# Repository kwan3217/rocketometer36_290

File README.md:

Moved to [GitHub](https://gitlab.com/kwan32171/rocketometer36_290)

This documents the data produced by the Rocketometer during NASA Sounding Rocket Flight 36.290, 2013 Oct 21.

# Encoding format
The data was captured and encoded in the form of CCSDS packets. The exact structure of each packet is most completely documented in the source code.

# Source code
The Rocketometer contains an LPC2148 ARM-based MCU with 512kiB flash memory. As this was far more memory than I needed for the firmware, I worked out a way to attach the source code of the firmware as well as the hardware design to the firmware itself. The Rocketometer spits this out into the packet stream as one of the first things it does at startup. How's that for configuration control?

The source code package is in the form of a ZPAQ TAR archive. The folder includes all the C++ source code, Makefiles, and such for rebuilding the firmware, which will be identical to the firmware carried on the flight with the exception of the date stamp on the firmware.

The hardware design is in the form of an Eagle CAD board and schematic, editable with the Eagle freeware version (as that is what it was designed with). It also includes a bill of materials in the form of Digikey catalog numbers for all parts used on the board.

The source code package is attached to the firmware, along with pointers to exactly where in the firmware the package begins and ends. This enables the firmware to copy a piece of itself into the packet stream as multiple CCSDS packets.

# Time Stamp
The firmware uses one of the MCU counter/timers for timing. This counter is a 32-bit unsigned number which starts at zero during firmware bootup, and counts up to one less than 3.6 billion counts exactly, at which point it resets to zero. The counter nominally runs at 60MHz, so this counter resets once every 60 seconds. Each time-sensitive packet (almost all of them except for some startup packets) have this count in it, and the packets are generated at such a rate that it is possible to unambiguously unwind the counter and get an exact number of counts since startup. Unfortunately the time of startup was not marked in any absolute time scale such as UTC, so absolute timing has to be inferred from timestamped events in the data.

# Sensor data
The sensor data stream consists of three separate streams of packets:
1. The Fast packet includes the MPU6050 3-axis acceleration, 3-axis rotation, and temperature readings, along with the ADXL377 3-axis high-acceleration readings. These were read once every 3 milliseconds and timestamped as indicated above.
2. The Compass packet includes the HMC5883 3-axis magnetic readouts. These were measured at a multiple of the Fast packet period (see the source code for details)
3. The BMP packet includes the BMP180 pressure and temperature readouts, both raw and calibrated into physical units.
4. The Power packet stream includes one packet each time the external power state changed (including one at startup).
5. The Vertical packet stream includes data on the vertical sensing fast/slow packet rate (see the source code for details). I have verified that this worked as intended, and that the entire flight was recorded at the fast rate.

# Packet storage
Packet storage was on a 16GB microSD card. Less than 1GB was used between the time I delivered the Rocketometer and the time it was returned to me.

# Power
The board consumes something around 100mA, not counting charging. The charger can use and additional 100mA. The system has an internal battery in the form of a 100mAh LiPo cell. The Rocketometer is powered externally by a 5V line from the rocket payload. It charges the battery with its on-board LiPo charging circuit as necessary when external power is available, and runs off the battery when external power is off. The on-board switch is not accessible, so the board is on whenever the rest of the rocket payload is on, and only turns off once its battery discharges. The battery is made safe by its standard integrated safety circuit and the dedicated LiPo charging circuit.

# The Flight
The Rocketometer was integrated with the rest of the rocket payload months before the flight. After that time, no human interaction whatsoever took place. It was returned to me for readout a couple of hours after the flight was completed. In that time, it recorded 65 files, one for each time it was power-cycled. The one containing the flight was file RKTO0620.SDS . This file contains 54.4 MB of data covering well over an hour, from about 35 minutes before the flight until well after impact. External power was cut 585 seconds after launch, and the on-board battery sustained it for the rest of the flight.

# Rail data
The file RKTO0620.SDS starts after the rail was raised to almost vertical. Other records were taken when the rail was horizontal, in particular RKTO0600.SDS. This data has been processed into the same tables and published. Interesting things such as orientation of the Rocketometer relative to the rail can be determined from that.

It would have been nice for the Rocketometer to have been recording while the rail was raised from horizontal to vertical. Unfortunately this did not happen. Maybe next time...

For whatever reason, it seems that no magnetic data was recorded while the rail was horizontal. Apparently magnetic data is not recorded when the board is recording at low rate.

# Rocketometer coordinate system
All sensors were co-aligned, so each individual sensor matches the whole Rocketometer frame. The Rocketometer was mounted close to the spin axis of the rocket, with the +Z axis pointed towards the tail. Consequently the thrust acceleration was primarily read out as a -Z acceleration. It should be parallel to that axis to within normal mechanical tolerances, almost certainly quite a bit better than 1°.

Based on the rail data, the +X axis of the Rocketometer was pointed almost straight down when the rocket was hanging horizontally from the rail.

In the flight after burnout but before spindown, the rocket was coasting well above the atmosphere and spinning with constant angular momentum, nearly around its long axis. Therefore the entire sensed acceleration is pure centripetal. Therefore, the distance and direction from the accelerometer to the spin axis can be measured. I did this once, but I wasn't sure about the signs and therefore didn't record it.

# Processing into tables
The packet stream format is not convenient or quick for import into IDL. For this purpose, a packet dumper, extractFast, was written in pure C which reads a Rocketometer data file, parses out each kind of packet, and writes each different apid into a different file. All the fast packets are together, all the slow packets, all the compass, all the source code, etc are each in their own file. Since the most common case is that each apid has a consistent length, this apid file can be read quickly into IDL by a read_binary, treating it as a 2D array of 16-bit integers, where rows are individual packets, and columns are fields in the packet.

Each packet is assigned a global sequence number, and this number is one of the things written to the APID file. With this sequence number, the order of different packets in different files can be determined.

These APID files are then imported into IDL, where the timestamps are normalized, values are converted in endian-ness as needed, and in general the packets are parsed. As this is an array operation, it can be done several orders of magnitude faster than parsing each packet individually in IDL.

The published tables have the timestamp normalized (cycle ambiguity fixed, converted into seconds, offset from power-on to launch subtracted) but otherwise the data is as recorded by the Rocketometer in flight. In particular, no translation from raw DNs to physical units is performed.

# Included files
* `RKTO0620.SDS.zip` - raw flight data file, PKZIP compressed
* `RKTO0600.SDS.zip` - raw rail data file, PKZIP compressed
* `firmware.tar.gz` - Firmware package, as flown (from RKTO0620.SDS) but zpaq uncompressed and gzip recompressed
* `extractFast.c` - C program described above
* `apid list.ods` - Some documentation of the packet format, not know to be completely up-to-date. Use the source code as the final authority.
* `import_fast.pro` - IDL program which converts extractFast output to CSV tables, among other things.
* `RKTO0620_csv.zip` - Compressed archive containing the following files
   * `RKTO0620_fast.csv` - Comma separated values, fast packets as described above
   * `RKTO0620_bmp.csv` - Comma separated values, BMP180 temperature and pressure readings, raw and calibrated into physical units by the Rocketometer in-flight
   * `RKTO0620_hmc.csv` - Comma separated values, HMC5883 magnetic readings, as described above.
* `RKTO0600_csv.zip` - Compressed archive containing the following files
   * `RKTO0600_fast.csv` - Comma separated values, fast packets as described above
   * `RKTO0600_bmp.csv` - Comma separated values, BMP180 temperature and pressure readings, raw and calibrated into physical units by the Rocketometer on-board

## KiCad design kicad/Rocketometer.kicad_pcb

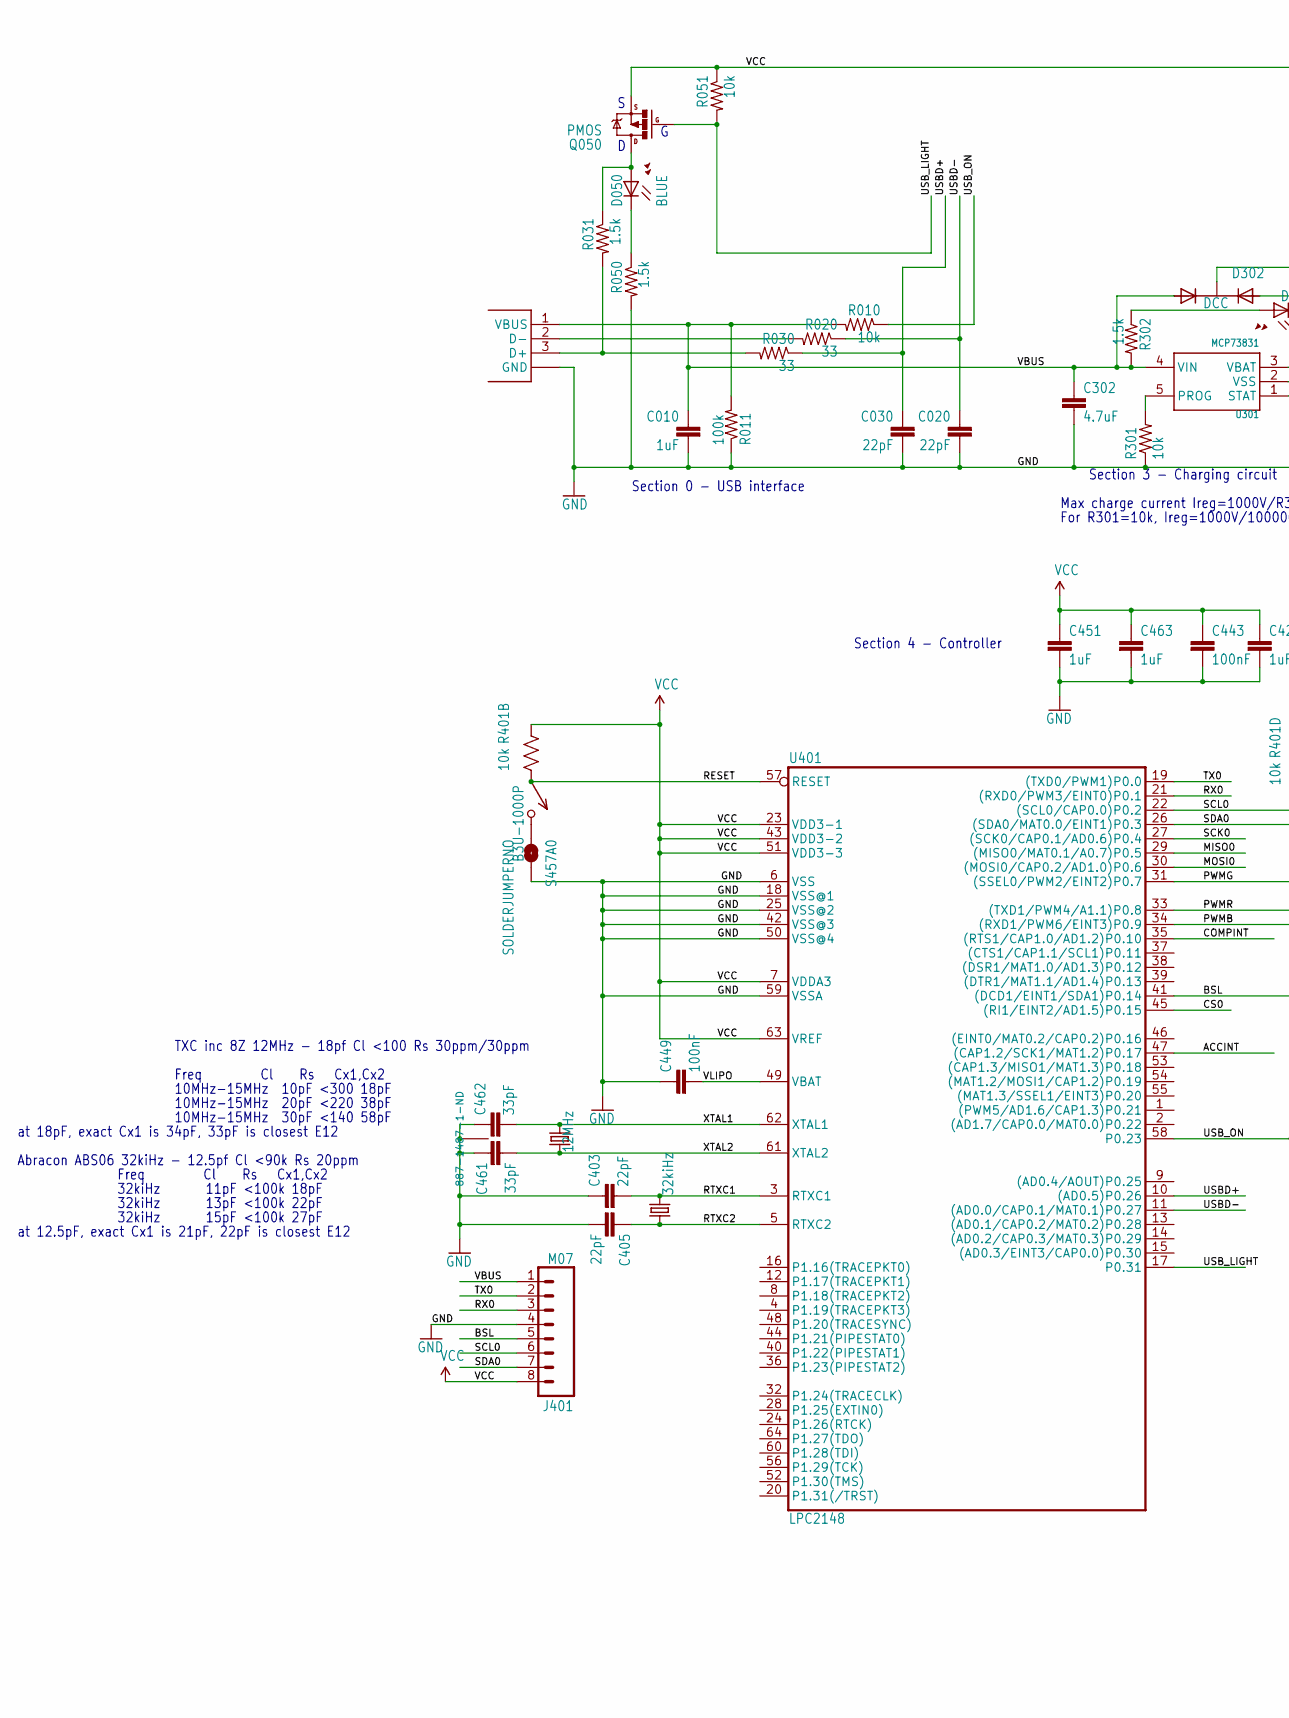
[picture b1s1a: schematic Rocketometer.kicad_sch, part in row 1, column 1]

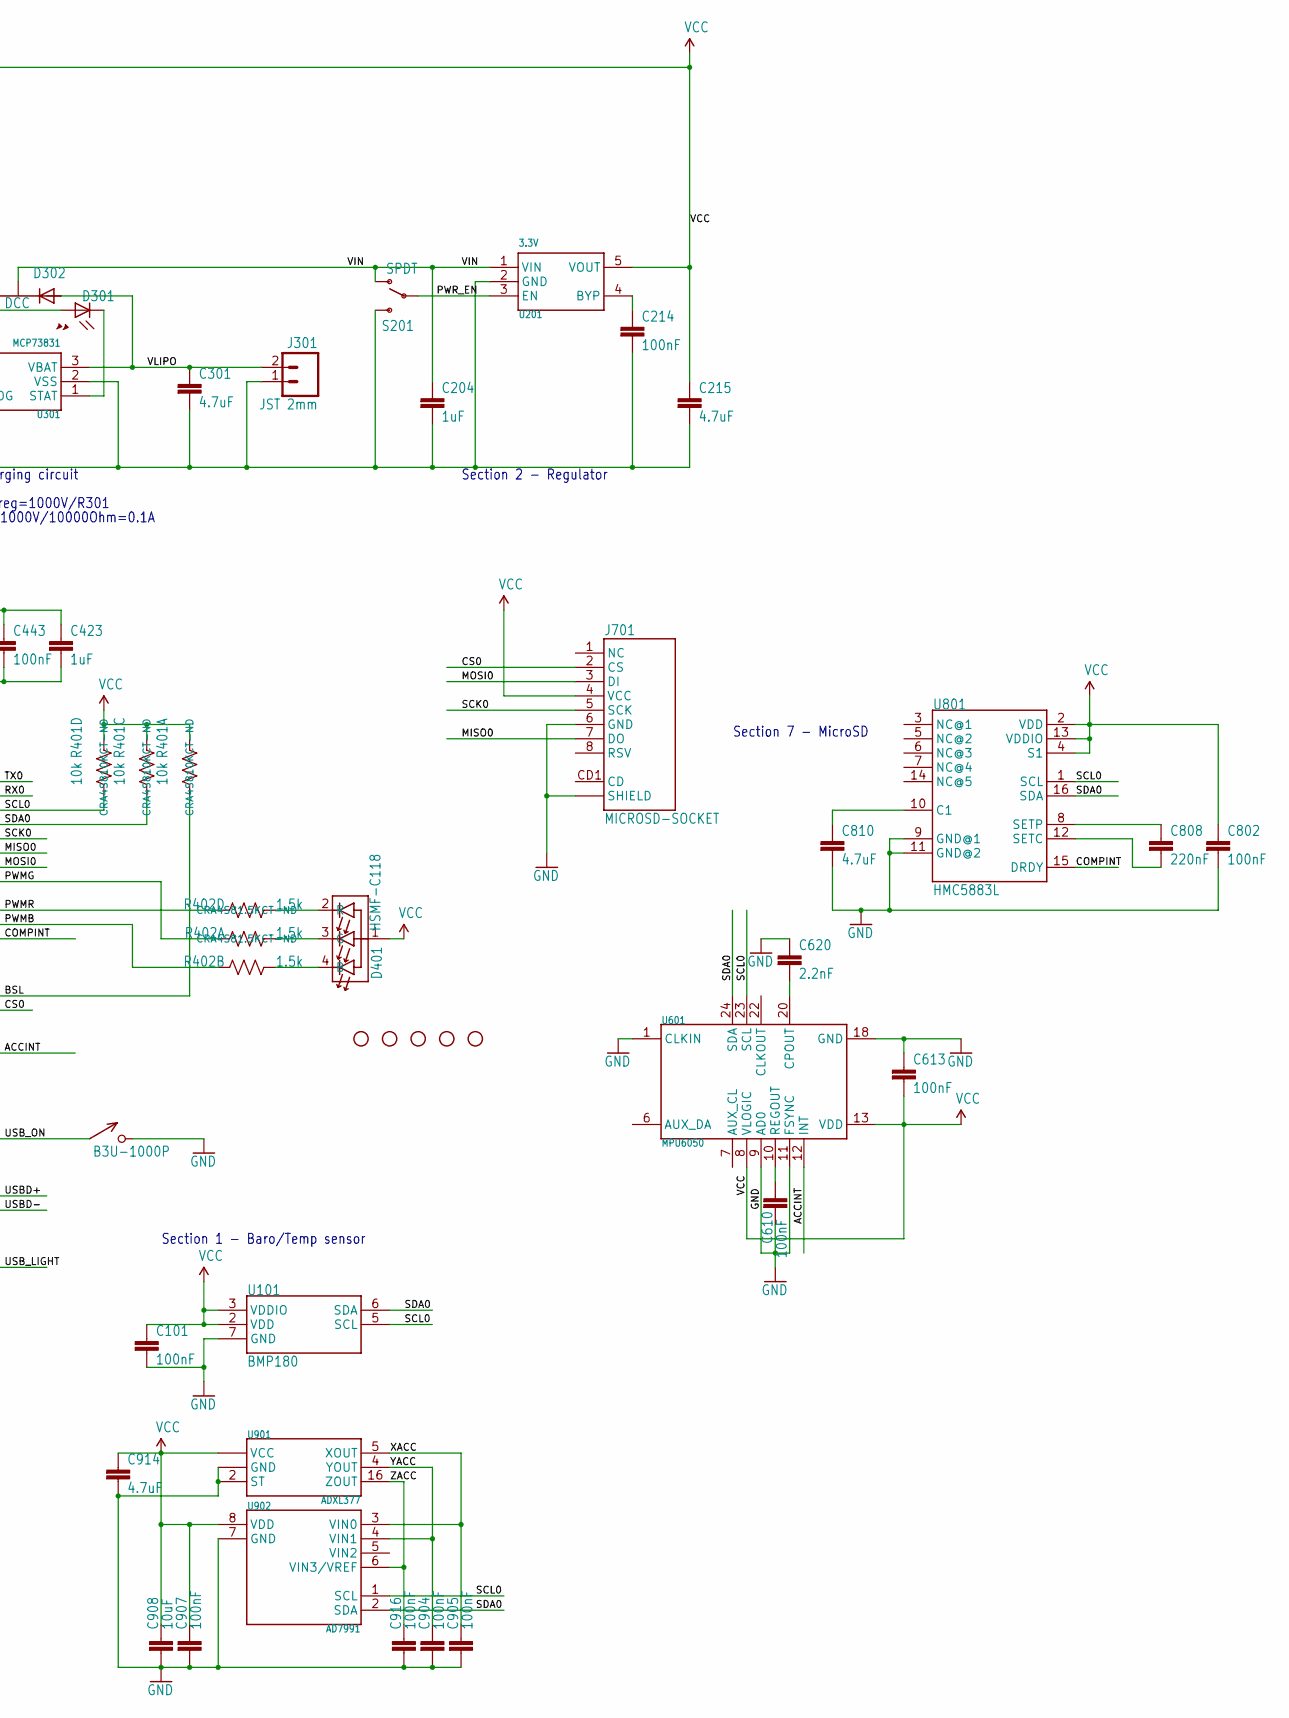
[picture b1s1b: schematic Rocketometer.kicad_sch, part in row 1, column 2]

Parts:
C010, C204, C423, C451, C463: 1uF; 0402-CAP; DIGIKEY 445-4114-1-ND
C020, C030, C403, C405: 22pF; 0402-CAP; DIGIKEY 445-1239-1-ND
C101, C214, C443, C449, C610, C613, C802, C904, C905, C907, C916: 100nF; 0402-CAP; DIGIKEY 445-1265-1-ND
C215, C301, C302, C810, C914: 4.7uF; 0402-CAP; DIGIKEY 445-7395-1-ND
C461, C462: 33pF; 0402-CAP; DIGIKEY 445-1241-1-ND
C620: 2.2nF; 0402-CAP; DIGIKEY 445-1257-1-ND
C808: 220nF; 0402-CAP; DIGIKEY 445-5938-1-ND
C908: 10uF; 0603-CAP; DIGIKEY 445-7486-1-ND
D050: BLUE; LED-0603; DIGIKEY 350-2037-1-ND
D301: YELLOW; LED-0603; DIGIKEY 350-2032-1-ND
D302: DCC; SOT-23-3; DIGIKEY 568-6500-1-ND
D401: HSMF-C118; DIGIKEY 516-1778-1-ND
J001: USB_MICROB_JST; UB-MC5BR3-SD204-4S; DIGIKEY 455-2562-1-ND
J301: JST 2mm; JST-2-SMD; DIGIKEY 455-1749-1-ND
J401: M07; 1X08; DIGIKEY $NOPART
J701: MICROSD-SOCKET; MICROSD-SOCKET-PP; DIGIKEY 101-00581-59-1-ND
JP1, JP2, JP3, JP4, JP5: STAND-OFFTIGHT; STAND-OFF-TIGHT; DIGIKEY $NOPART
Q050: PMOS; SOT23-3; DIGIKEY NTR1P02T1GOSCT-ND
R010, R051, R301: 10k; 0402-RES; DIGIKEY P10.0KLCT-ND
R011: 100k; 0402-RES; DIGIKEY P100KLCT-ND
R020, R030: 33; 0402-RES; DIGIKEY P33.0LCT-ND
R031, R050, R302: 1.5k; 0402-RES; DIGIKEY P1.50KLCT-ND
R401: 10k; CRA04; DIGIKEY CRA4S810KCT-ND
R402: 1.5k; CRA04; DIGIKEY CRA4S81.5KCT-ND
S201: SPDT; AYZ0202; DIGIKEY 401-2013-1-ND
S457, S458: B3U-1000P; DIGIKEY SW1020CT-ND
S457A0: SOLDERJUMPERNO; SJ_2S-NO; DIGIKEY $NOPART
U101: BMP180; DIGIKEY 828-1027-1-ND
U201: 3.3V; SOT-23-5; DIGIKEY 576-1910-1-ND
U301: MCP73831; SOT-23-5; DIGIKEY 576-1910-1-ND
U401: LPC2148; SQFP-S-10X10-64; DIGIKEY 568-1765-ND
U601: MPU6050; MPU60X0; DIGIKEY $NOPART
U801: HMC5883L; 16LPCC; DIGIKEY 342-1082-1-ND
U901: ADXL377; DIGIKEY ADXL377BCPZ-RL7CT-ND
U902: AD7991; SOT-23-8; DIGIKEY AD7991YRJZ-0500RL7CT-ND
Y401: 12MHz; CRYSTAL_SMD_2MM_2_5MM; DIGIKEY 887-1487-1-ND
Y402: 32kiHz; ABS06; DIGIKEY 535-10104-1-ND

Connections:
ACCINT: U401.47 ((CAP1.2/SCK1/MAT1.2)P0.17), U601.12 (INT)
BSL: J401.5, R401.1, U401.41 ((DCD1/EINT1/SDA1)P0.14)
COMPINT: U401.35 ((RTS1/CAP1.0/AD1.2)P0.10), U801.15 (DRDY)
CONN_D+: J001.3 (D+), R030.2, R031.2
CONN_D-: J001.2 (D-), R020.2
CS0: J701.2 (CS), U401.45 ((RI1/EINT2/AD1.5)P0.15)
GND: C010.2, C020.2, C030.2, C101.2, C204.2, C214.2, C215.2, C301.2, C302.2, C403.1, C405.2, C423.2, C443.2, C449.1, C451.2, C461.1, C462.1, C463.2, C610.2, C613.1, C620.1, C802.2, C810.2, C904.2, C905.2, C907.2, C908.2, C914.2, C916.2, J001.5 (GND), J001.P$6 (GND), J001.P$7 (GND), J001.P$8 (GND), J001.P$9 (GND), J001.P$10 (GND), J001.P$11 (GND), J301.1, J401.4, J701.6 (GND), J701.CD2 (SHIELD), J701.GND1 (SHIELD), J701.GND3 (SHIELD), R011.1, R050.2, R301.1, S201.3 (S), S457A0.2, S458.P$2 (2), U101.7 (GND), U201.2 (GND), U301.2 (VSS), U401.6 (VSS), U401.18 (VSS@1), U401.25 (VSS@2), U401.42 (VSS@3), U401.50 (VSS@4), U401.59 (VSSA), U601.1 (CLKIN), U601.9 (AD0), U601.11 (FSYNC), U601.18 (GND), U801.9 (GND@1), U801.11 (GND@2), U901.2 (ST), U901.6 (GND), U901.7 (GND), U902.7 (GND), Y401.2 (1), Y401.4 (1)
MISO0: J701.7 (DO), U401.29 ((MISO0/MAT0.1/A0.7)P0.5)
MOSI0: J701.3 (DI), U401.30 ((MOSI0/CAP0.2/AD1.0)P0.6)
unnamed: C620.2, U601.20 (CPOUT)
unnamed: R301.2, U301.5 (PROG)
unnamed: D301.C, U301.1 (STAT)
unnamed: D301.A, R302.1
unnamed: D050.A, Q050.3 (D), R031.1
unnamed: D050.C, R050.1
unnamed: S457.P$2 (2), S457A0.1
unnamed: C610.1, U601.10 (REGOUT)
unnamed: C808.1, U801.8 (SETP)
unnamed: C808.2, U801.12 (SETC)
unnamed: C810.1, U801.10 (C1)
unnamed: C214.1, U201.4 (BYP)
PWMB: R402.7 (2), U401.34 ((RXD1/PWM6/EINT3)P0.9)
PWMG: R402.8 (2), U401.31 ((SSEL0/PWM2/EINT2)P0.7)
PWMR: R402.5 (2), U401.33 ((TXD1/PWM4/A1.1)P0.8)
PWR_EN: S201.2, U201.3 (EN)
QWMB: D401.4 (B), R402.2 (1)
QWMG: D401.3 (G), R402.1
QWMR: D401.2 (R), R402.4 (1)
RESET: R401.2 (1), S457.P$1 (1), U401.57 (RESET)
RTXC1: C403.2, U401.3 (RTXC1), Y402.2
RTXC2: C405.1, U401.5 (RTXC2), Y402.1
RX0: J401.3, U401.21 ((RXD0/PWM3/EINT0)P0.1)
SCK0: J701.5 (SCK), U401.27 ((SCK0/CAP0.1/AD0.6)P0.4)
SCL0: J401.6, R401.4 (1), U101.5 (SCL), U401.22 ((SCL0/CAP0.0)P0.2), U601.23 (SCL), U801.1 (SCL), U902.1 (SCL)
SDA0: J401.7, R401.3 (1), U101.6 (SDA), U401.26 ((SDA0/MAT0.0/EINT1)P0.3), U601.24 (SDA), U801.16 (SDA), U902.2 (SDA)
TX0: J401.2, U401.19 ((TXD0/PWM1)P0.0)
USBD+: C030.1, R030.1, U401.10 ((AD0.5)P0.26)
USBD-: C020.1, R020.1, U401.11 ((AD0.0/CAP0.1/MAT0.1)P0.27)
USB_LIGHT: Q050.1 (G), R051.2, U401.17 (P0.31)
USB_ON: R010.1, S458.P$1 (1), U401.58 (P0.23)
VBUS: C010.1, C302.1, D302.1 (A1), J001.1 (VBUS), J401.1, R010.2, R011.2, R302.2, U301.4 (VIN)
VCC: C101.1, C215.1, C423.1, C443.1, C451.1, C463.1, C613.2, C802.1, C907.1, C908.1, C914.1, D401.1 (A), J401.8, J701.4 (VCC), Q050.2 (S), R051.1, R401.5 (2), R401.6 (2), R401.7 (2), R401.8 (2), U101.2 (VDD), U101.3 (VDDIO), U201.5 (VOUT), U401.7 (VDDA3), U401.23 (VDD3-1), U401.43 (VDD3-2), U401.51 (VDD3-3), U401.63 (VREF), U601.8 (VLOGIC), U601.13 (VDD), U801.2 (VDD), U801.4 (S1), U801.13 (VDDIO), U901.14 (VCC), U901.15 (VCC), U902.8 (VDD)
VIN: C204.1, D302.3 (K), S201.1 (O), U201.1 (VIN)
VLIPO: C301.1, C449.2, D302.2 (A2), J301.2, U301.3 (VBAT), U401.49 (VBAT)
XACC: C905.1, U901.5 (XOUT), U902.3 (VIN0)
XTAL1: C462.2, U401.62 (XTAL1), Y401.3 (2)
XTAL2: C461.2, U401.61 (XTAL2), Y401.1
YACC: C904.1, U901.4 (YOUT), U902.4 (VIN1)
ZACC: C916.1, U901.16 (ZOUT), U902.6 (VIN3/VREF)

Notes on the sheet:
10MHz-15MHz 30pF <140 58pF
10MHz-15MHz 10pF <300 18pF
Section 4 - Controller
Section 7 - MicroSD
Section 2 - Regulator
10MHz-15MHz 20pF <220 38pF
32kiHz 13pF <100k 22pF
Section 0 - USB interface
For R301=10k, Ireg=1000V/10000Ohm=0.1A
32kiHz 11pF <100k 18pF
Section 1 - Baro/Temp sensor
32kiHz 15pF <100k 27pF
TXC inc 8Z 12MHz - 18pf Cl <100 Rs 30ppm/30ppm
Freq Cl Rs Cx1,Cx2
Section 3 - Charging circuit
Max charge current Ireg=1000V/R301
at 12.5pF, exact Cx1 is 21pF, 22pF is closest E12
at 18pF, exact Cx1 is 34pF, 33pF is closest E12
Abracon ABS06 32kiHz - 12.5pf Cl <90k Rs 20ppm

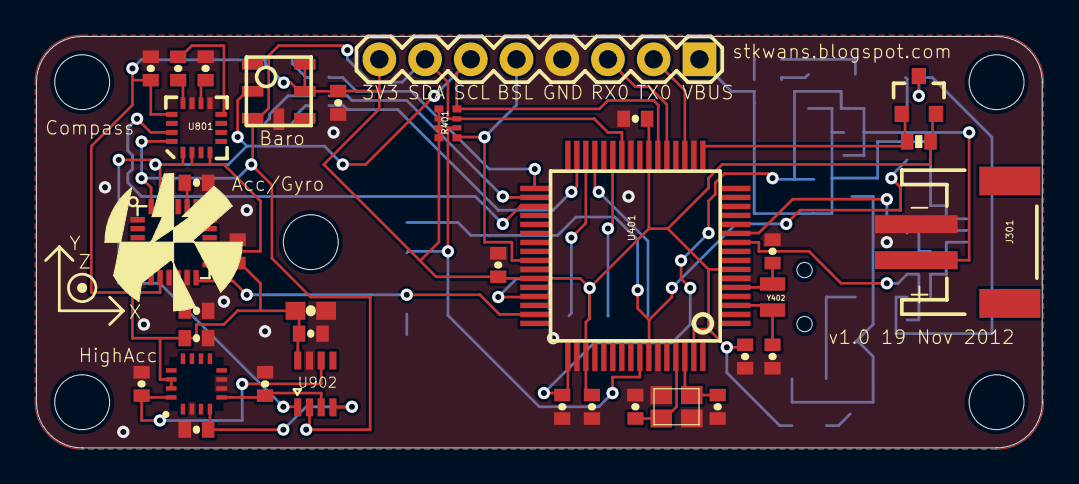
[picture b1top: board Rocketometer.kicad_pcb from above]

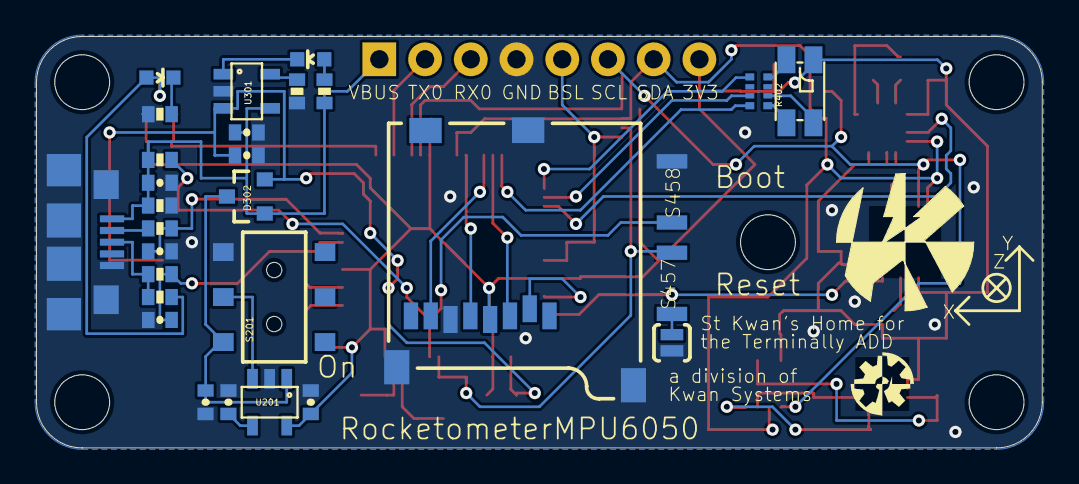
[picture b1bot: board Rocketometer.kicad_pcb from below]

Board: 2 copper layers, 55.9 x 22.9 mm, 73 parts (31 on the bottom side), 49 nets.

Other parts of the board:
U$1, U$5: KWAN_ACC
U$4: AXES
U$6: OSHW_ACC

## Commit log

2025-12-30 Initial commit, exactly as downlinked in firmware.tar.gz as extracted from RKTO0620.SDS
2025-12-30 Initial commit of firmware.tar.gz exactly as extracted from RKTO0620.SDS
2025-12-30 Add README.md copied from `https://docs.google.com/document/d/16n48eKw8qXVwFw7mPsXVgNxVIUt9RdN1GyR1KXHj5as/edit?tab=t.0#heading=h.q7tncahyum1`
2025-12-30 Add extract and import scripts
2026-01-02 Add python scripts to figure bounding box of a VRML wrl object and to find and sort lists of images in a folder tree.
2026-01-02 Add answers to portfolio interview questions
2026-01-02 add another .gitignore
2026-01-02 Add kicad import of Rocketometer as extracted from Eagle files from RKTO0620.SDS
2026-05-25 Update README to reflect new GitHub location
